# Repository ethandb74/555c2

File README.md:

# 555c2
A LED chaser which blinks 10 LEDS in a variable speed sequence. This pcb has a space theme with the leds tracing out the Big Dipper, my personal favorite constilation. I also included some hand drawn PCB art. This Project was done to develop PCB and Schematic skills. 

Below is an image of the front of my PCB.

Keep in mind this photo does not contain the connectors which were added after the photot was taken.

Below is my Schematic:

My PCB: 

Soldering the Board

Product:

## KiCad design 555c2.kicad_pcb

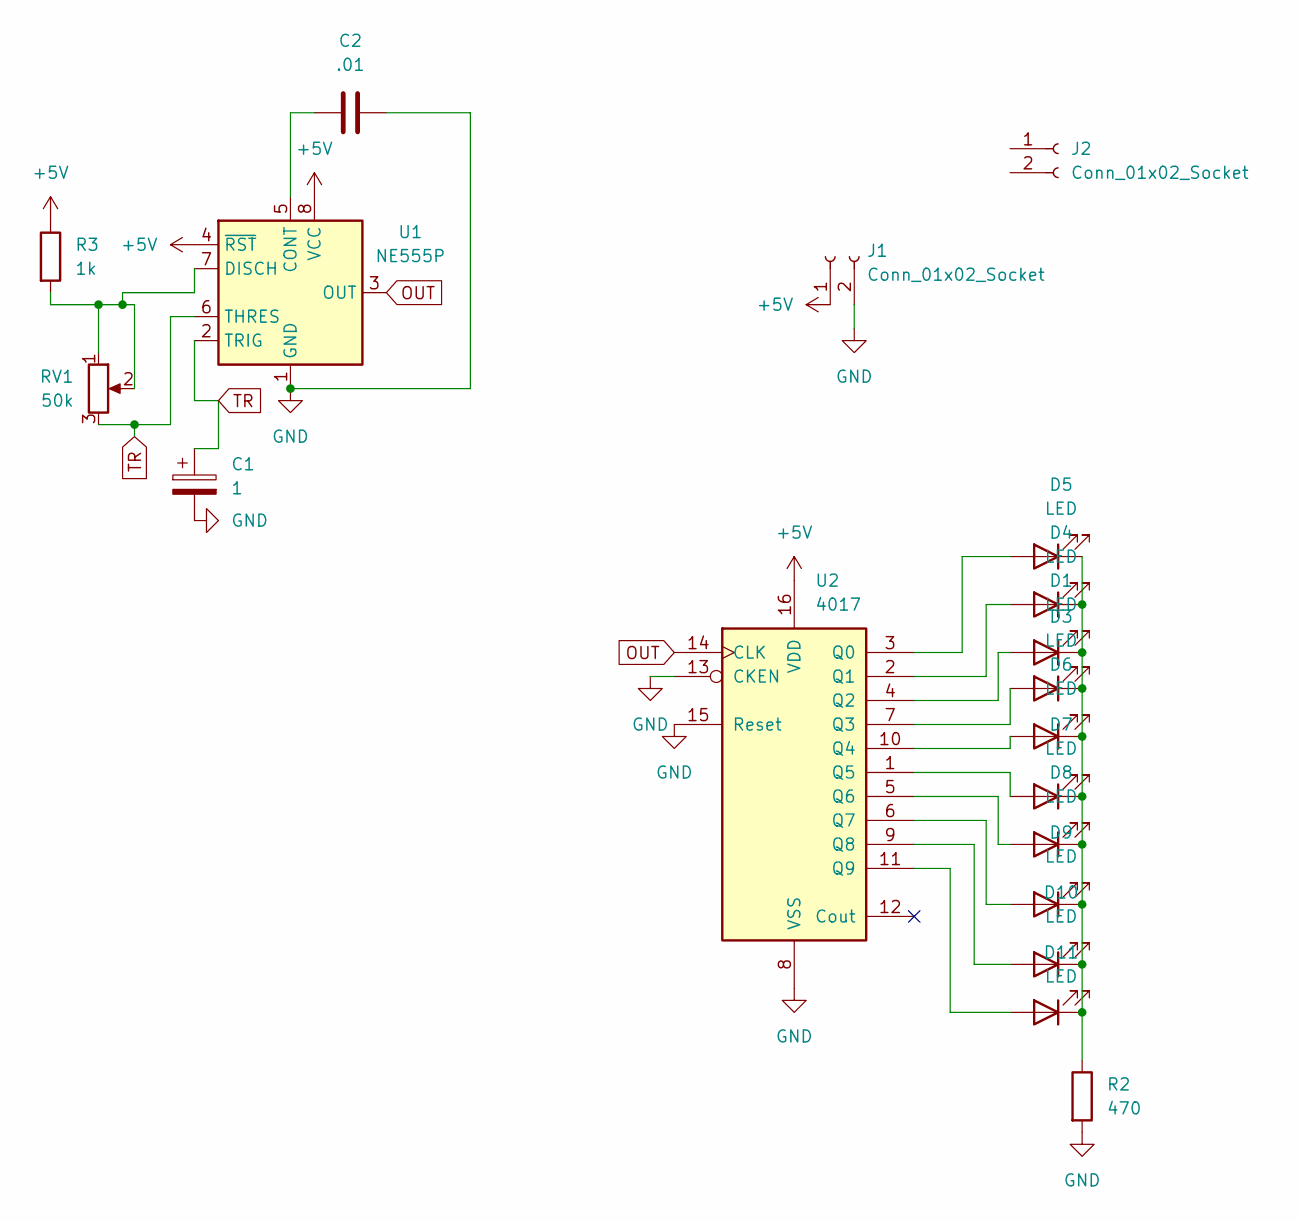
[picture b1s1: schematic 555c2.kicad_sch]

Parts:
C1: 1; C_Disc_D16.0mm_W5.0mm_P10.00mm
C2: .01; C_Radial_D5.0mm_H5.0mm_P2.00mm
D1, D3, D4, D5, D6, D7, D8, D9, D10, D11: LED; LED_D5.0mm
J1, J2: Conn_01x02_Socket; PinSocket_1x02_P2.54mm_Vertical
R2: 470; R_Axial_DIN0207_L6.3mm_D2.5mm_P7.62mm_Horizontal
R3: 1k; R_Axial_DIN0207_L6.3mm_D2.5mm_P7.62mm_Horizontal
RV1: 50k; Potentiometer_Bourns_PTV09A-1_Single_Vertical
U1: NE555P; DIP-8_W7.62mm
U2: 4017; N16

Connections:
+5V: J1.1, R3.1, U1.4 (~RST), U1.8 (VCC), U2.16 (VDD)
GND: C1.2, C2.2, J1.2, R2.2, U1.1 (GND), U2.8 (VSS), U2.13 (CKEN), U2.15 (Reset)
unnamed: D1.2 (A), U2.4 (Q2)
unnamed: D1.1 (K), D3.1 (K), D4.1 (K), D5.1 (K), D6.1 (K), D7.1 (K), D8.1 (K), D9.1 (K), D10.1 (K), D11.1 (K), R2.1
unnamed: D3.2 (A), U2.7 (Q3)
unnamed: D4.2 (A), U2.2 (Q1)
unnamed: D5.2 (A), U2.3 (Q0)
unnamed: D6.2 (A), U2.10 (Q4)
unnamed: D7.2 (A), U2.1 (Q5)
unnamed: D8.2 (A), U2.5 (Q6)
unnamed: D9.2 (A), U2.6 (Q7)
unnamed: D10.2 (A), U2.9 (Q8)
unnamed: D11.2 (A), U2.11 (Q9)
unnamed: C2.1, U1.5 (CONT)
unnamed: R3.2, RV1.1, RV1.2, U1.7 (DISCH)
OUT: U1.3 (OUT), U2.14 (CLK)
TR: C1.1, RV1.3, U1.2 (TRIG), U1.6 (THRES)

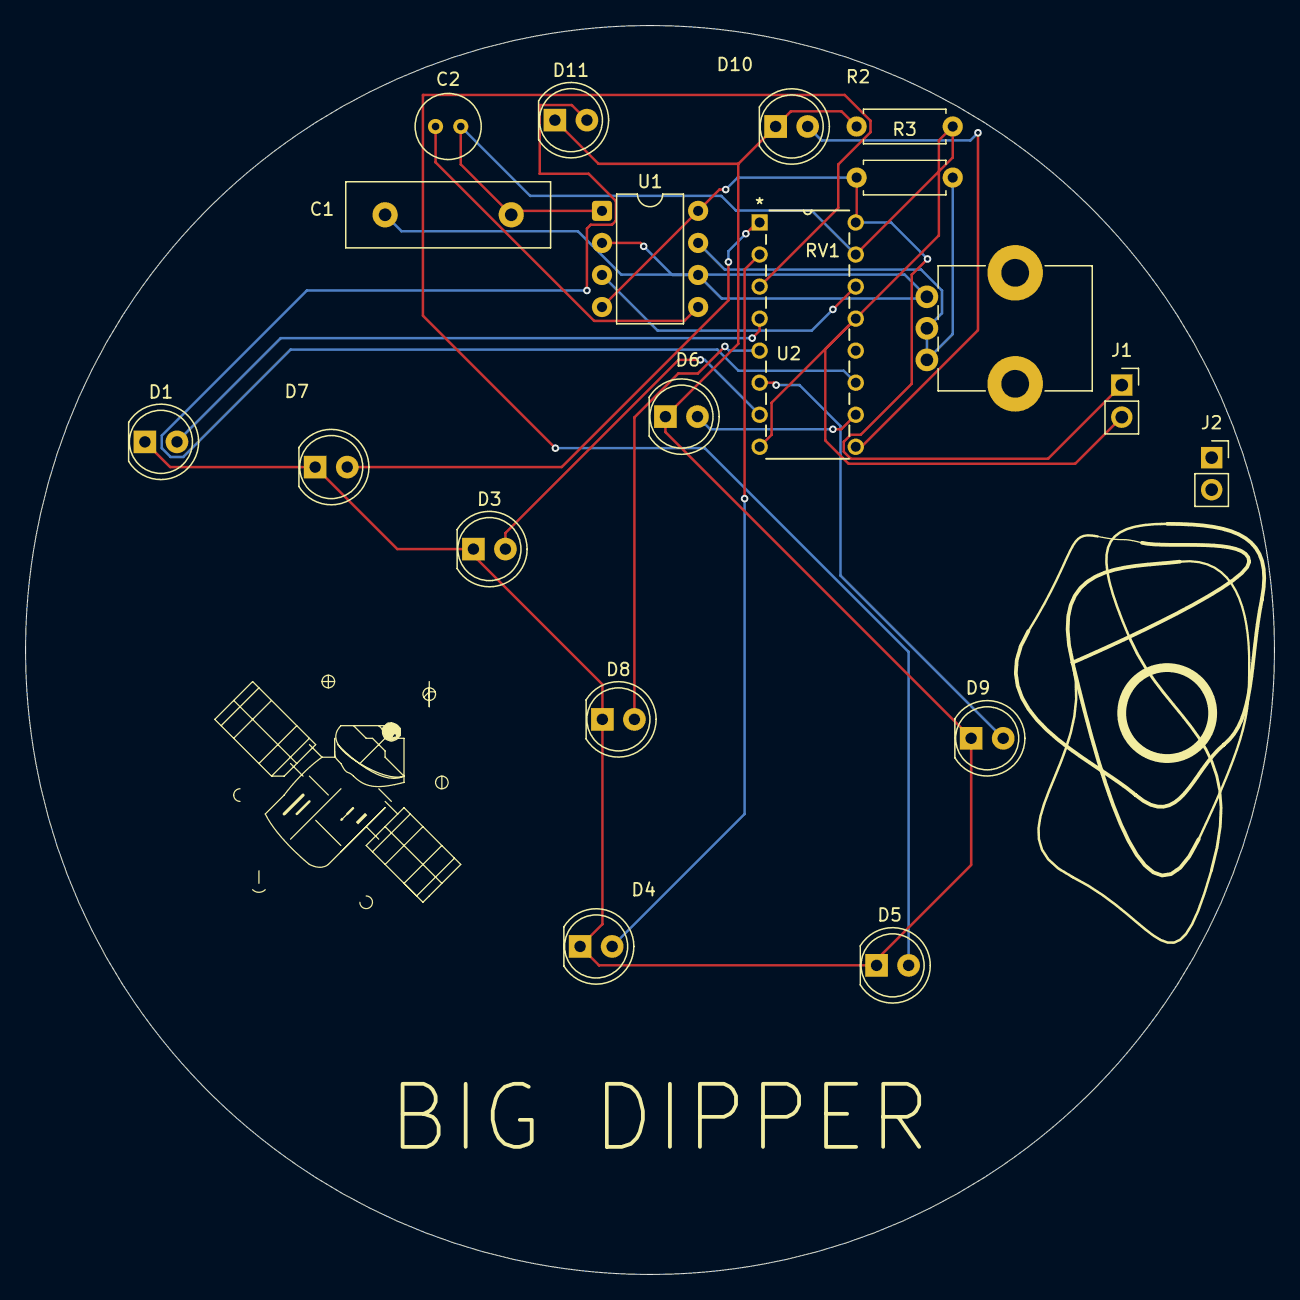
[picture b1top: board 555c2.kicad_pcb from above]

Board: 2 copper layers, 99.0 x 99.0 mm, 19 parts (0 on the bottom side), 17 nets.

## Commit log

2026-03-27 Add files via upload
    Theres are all my files:
    2 screenshots of PCB+
    .kicad_pro (KiCad project file)
    .kicad_sch (schematic, if you used KiCad)
    .kicad_pcb (PCB, if you used KiCad)
    Gerbers
2026-03-27 Update README.md
    fix readme
2026-03-27 new folders with a fixed bug
2026-03-28 Rename 555c2.kicad_pcb to pcb/555c2.kicad_pcb
2026-03-28 Rename 3dnew.png to assets/3dnew.png
2026-03-28 Rename 555c2_Gebers.zip to assets/555c2_Gebers.zip
2026-03-28 Rename 555c2.kicad_pro to assests/555c2.kicad_pro
2026-03-28 Rename 555c2.kicad_sch to sch/555c2.kicad_sch
2026-03-28 Rename 555c2.kicad_pro to 555c2.kicad_pro
2026-03-28 Rename 3dnew.png to 3dnew.png
2026-03-28 Rename Screenshot 2026-03-28 151842.png to images/Screenshot 2026-03-28 151842.png
2026-03-28 Rename 555c2.kicad_sch to 555c2.kicad_sch
